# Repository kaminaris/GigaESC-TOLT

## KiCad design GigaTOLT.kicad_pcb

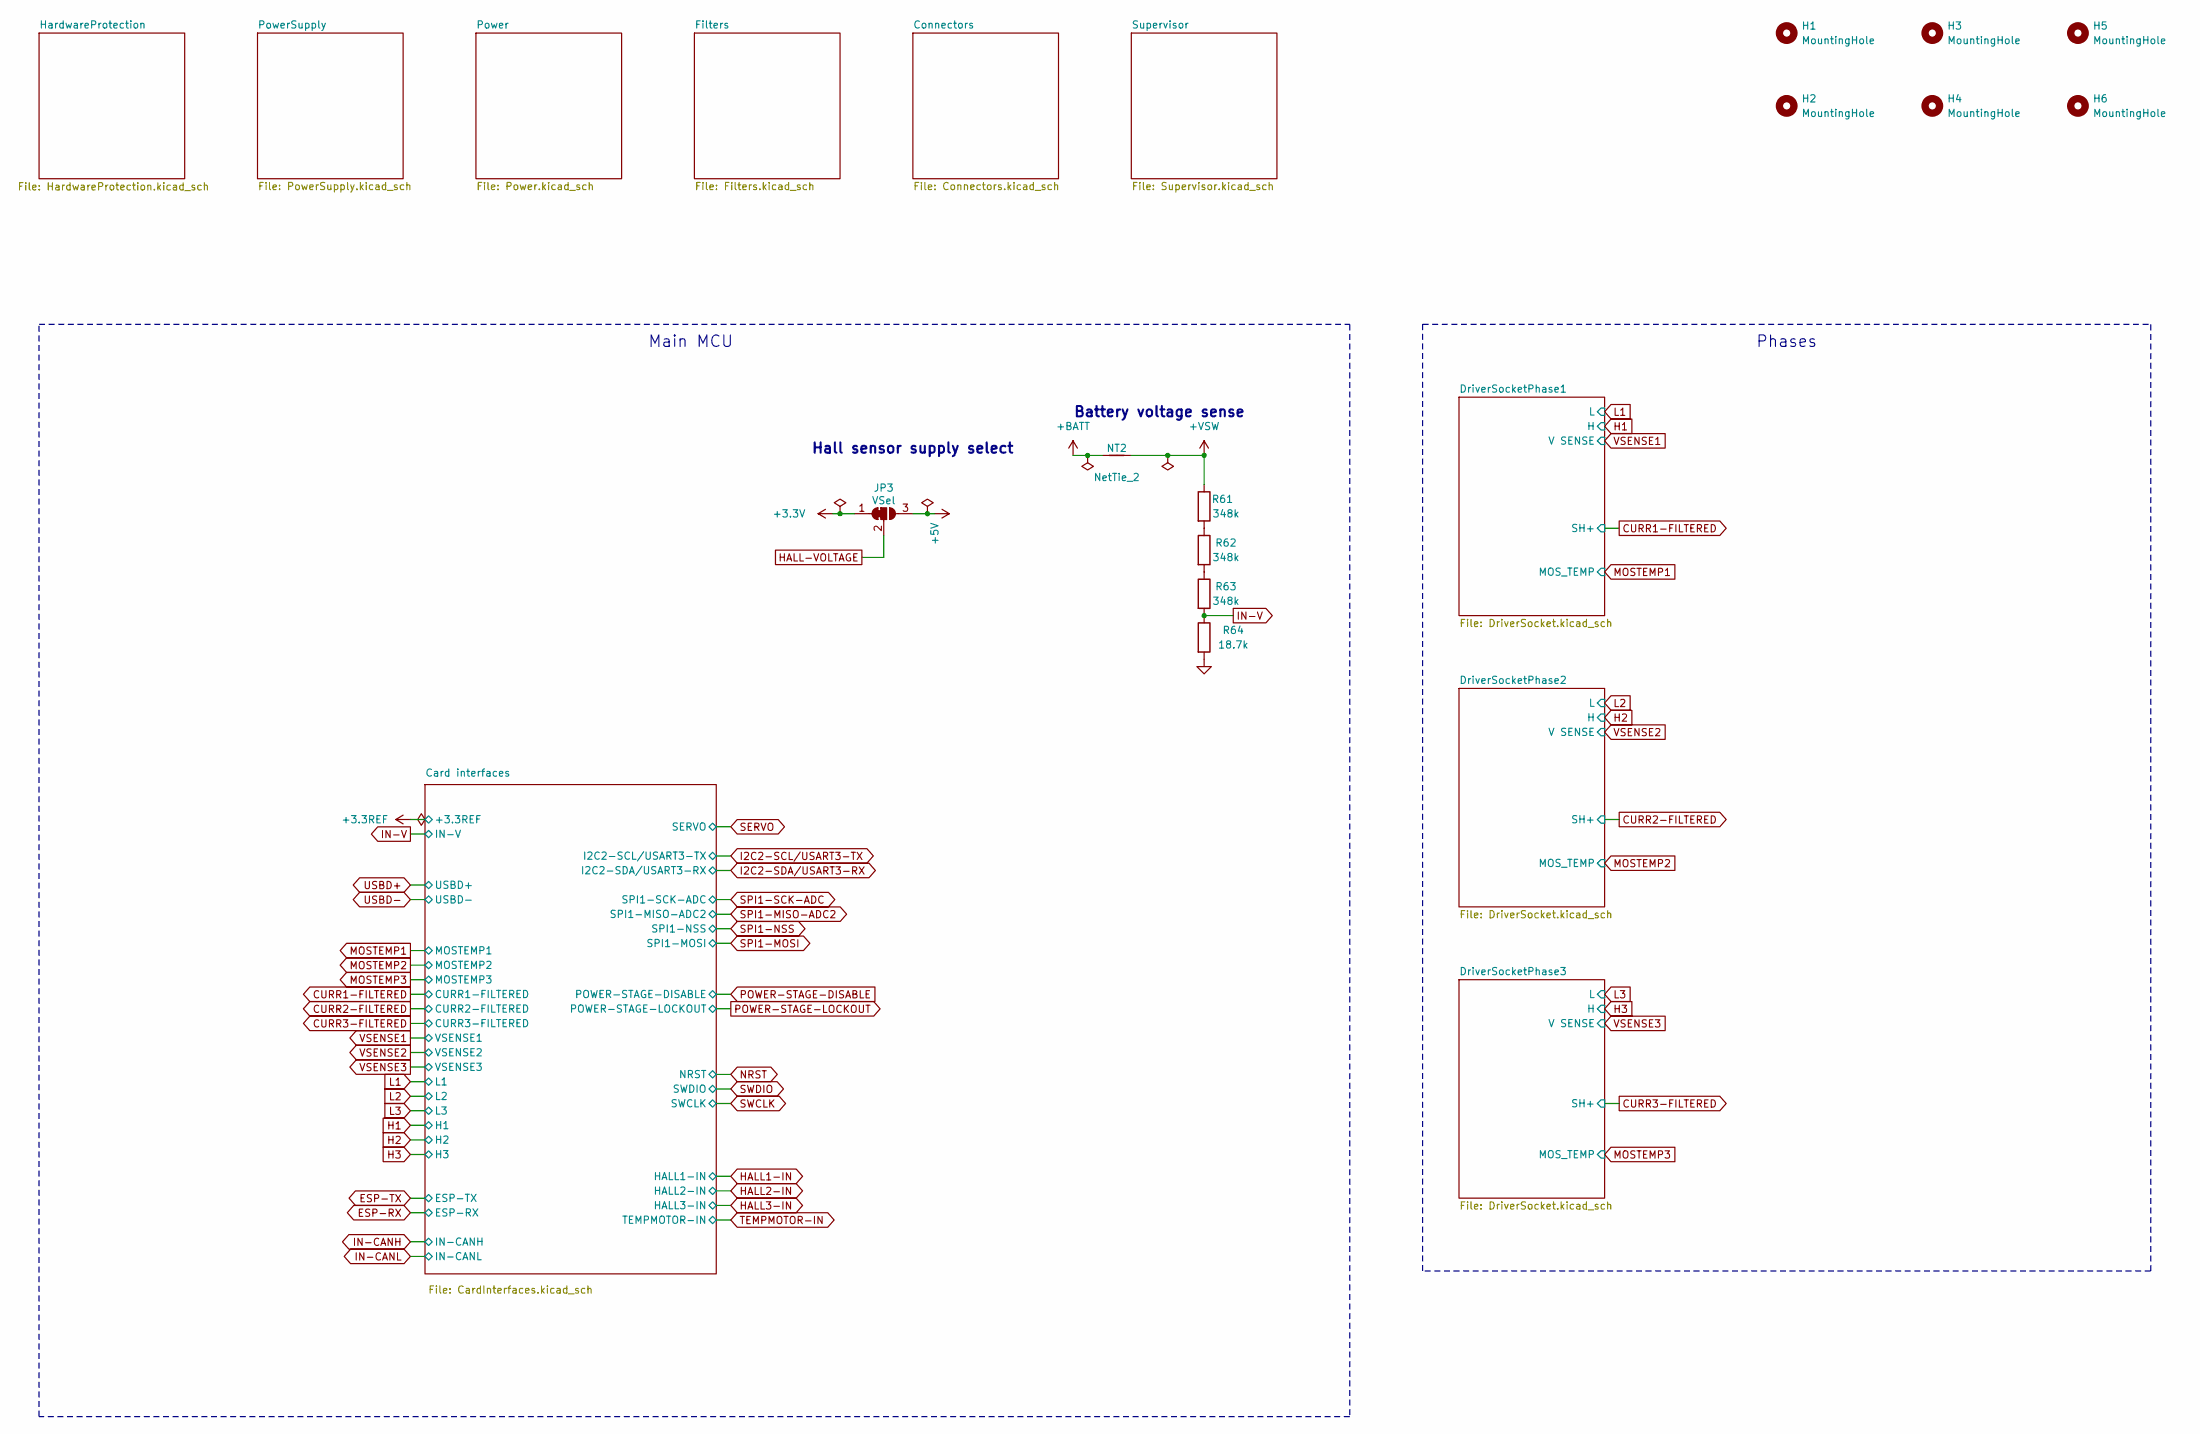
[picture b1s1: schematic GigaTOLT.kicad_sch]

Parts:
H1, H2, H3, H4, H5, H6: MountingHole; CapHead_3.5mm
JP3: VSel; SolderJumper-3-0.5-Small
NT2: NetTie_2; NetTie-2_SMD_Pad0.5mm
R61, R62, R63: 348k; R_0603_1608Metric; MPN C23006
R64: 18.7k; R_0603_1608Metric; MPN C22893

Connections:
+3.3V: JP3.1 (A); also elsewhere on the board
+5V: JP3.3 (B); also elsewhere on the board
+BATT: NT2.1; also elsewhere on the board
+VSW: NT2.2, R61.1; also elsewhere on the board
GND: R64.2; also elsewhere on the board
HALL-VOLTAGE: JP3.2 (C); also elsewhere on the board
IN-V: R63.2, R64.1; also elsewhere on the board
unnamed: R61.2, R62.1
unnamed: R62.2, R63.1

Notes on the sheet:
Main MCU
Battery voltage sense
Phases
Hall sensor supply select

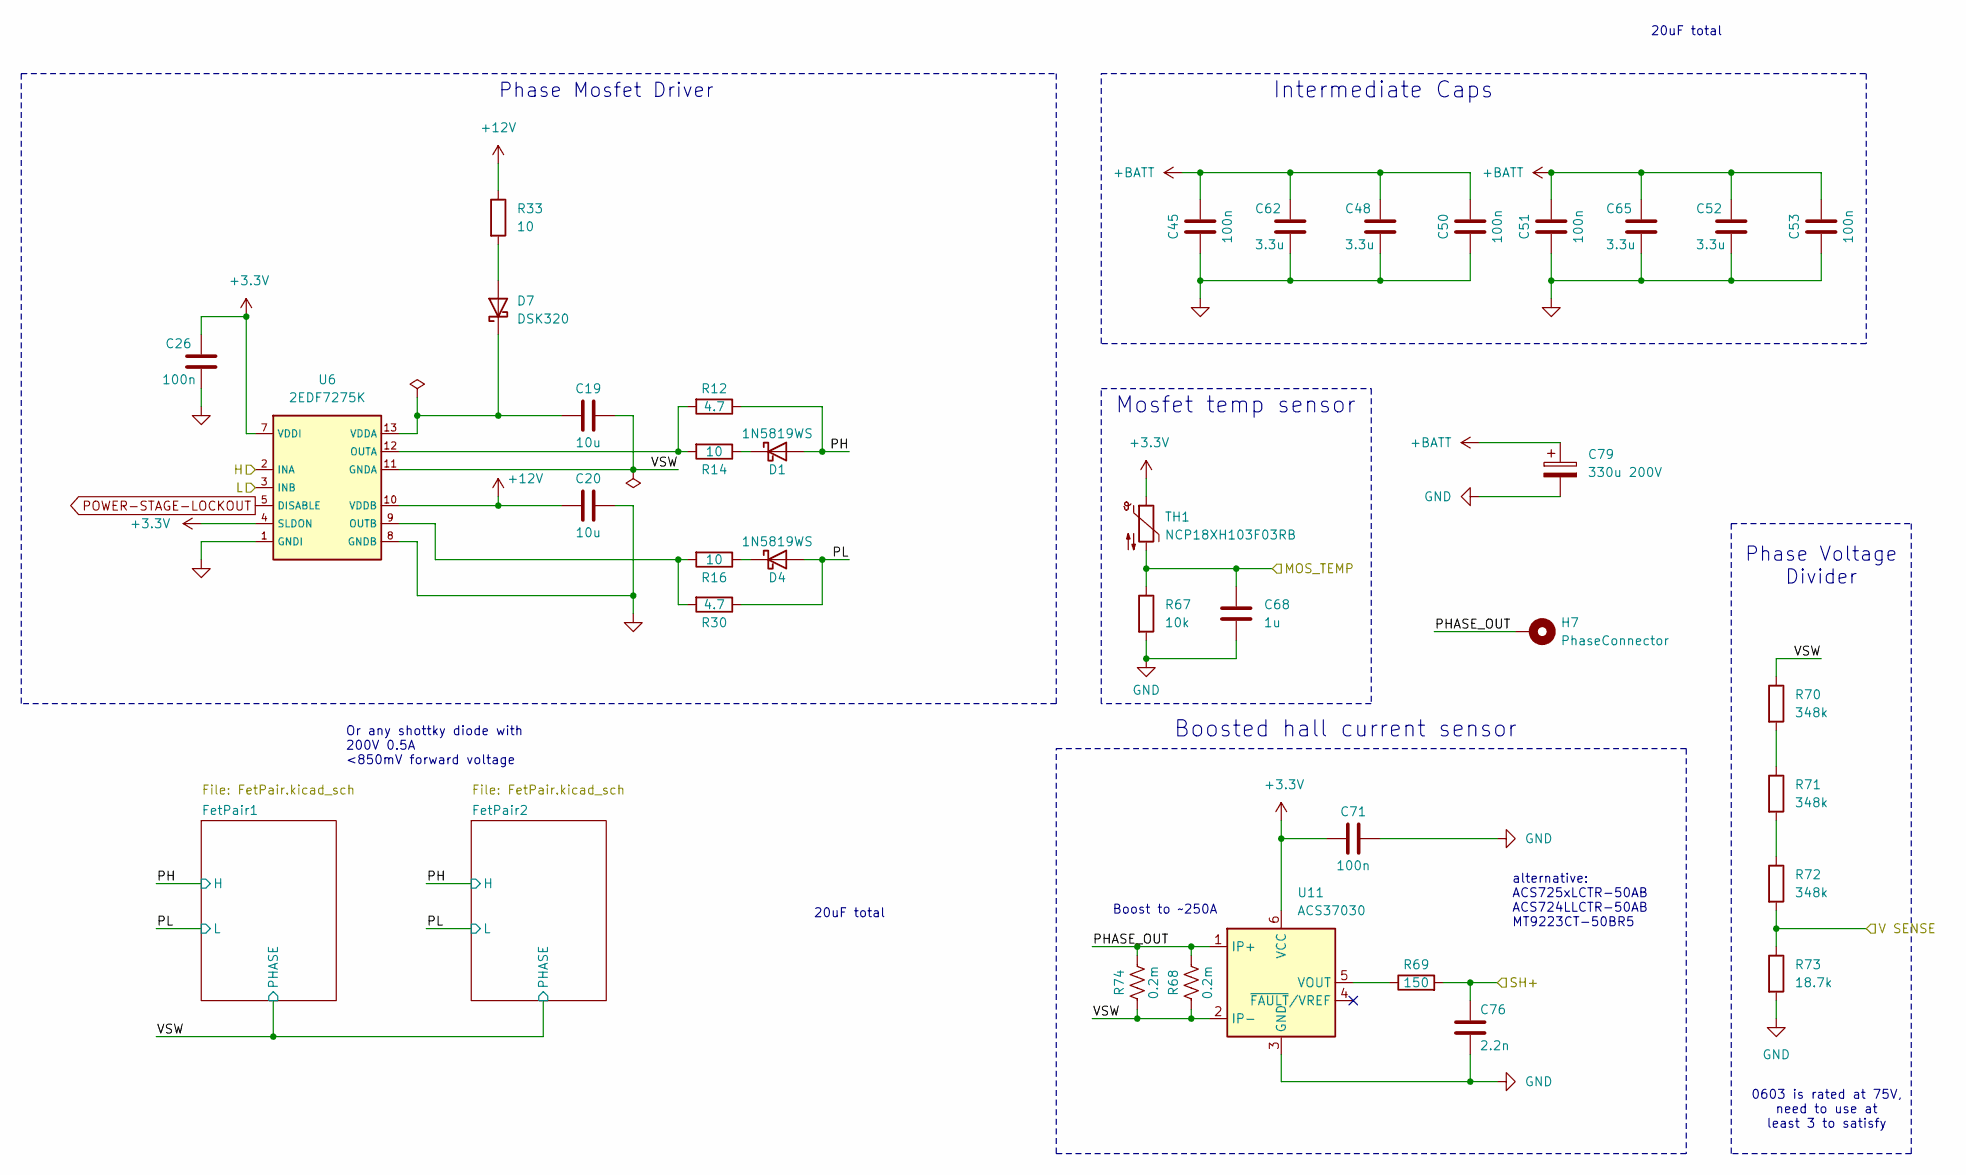
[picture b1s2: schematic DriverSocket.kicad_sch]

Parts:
C19, C20: 10u; C_0805_2012Metric; MPN C1779; Mouser 81-GRM319R61H475KA2D
C26, C71: 100n; C_0603_1608Metric; MPN C14663; Mouser 187-CL21B104KBFNNNE
C45, C50, C51, C53: 100n; C_0805_2012Metric; MPN C784084
C48, C52, C62, C65: 3.3u; C_2220_5750Metric; MPN C22370027; Mouser 81-GRM32EC72A106KE5K
C68: 1u; C_0603_1608Metric; MPN C15849; Mouser 187-CL21B105KPFNNNE
C76: 2.2n; C_0603_1608Metric; MPN C1604
C79: 330u 200V; CapacitorD18x32; MPN C697601; Mouser 661-EKMR201VS222MR50
D1, D4: 1N5819WS; D_SOD-323_HandSoldering; MPN C191023; Mouser 750-SS520B-HF
D7: DSK320; D_SOD-123; MPN C5290222; Mouser 750-SS520B-HF
H7: PhaseConnector; WP-RAFU_7461112
R12, R30: 4.7; R_0603_1608Metric; MPN C22939; Mouser 603-RC0805JR-072R2L
R14, R16, R33: 10; R_0603_1608Metric; MPN C22939; Mouser 603-RC0805JR-072R2L
R67: 10k; R_0603_1608Metric; MPN C25804; Mouser 708-RNCP0805FTD10K0
R68, R74: 0.2m; R_2512_6332Metric; MPN C4944115
R69: 150; R_0603_1608Metric; MPN C22808
R70, R71, R72: 348k; R_0603_1608Metric; MPN C23006; Mouser 603-RC0805FR-07100KL
R73: 18.7k; R_0603_1608Metric; MPN C22893; Mouser 71-CRCW0805-1.8K-E3
TH1: NCP18XH103F03RB; R_0603_1608Metric; MPN C13564; Mouser 81-NCP18XH103F03RB
U6: 2EDF7275K; IC_2EDF7275KXUMA2; MPN C2677063
U11: ACS37030; SOIC-6_3.9x4.9mm_P1.27mm; MPN C22406095

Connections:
+3.3V: C26.2, C71.2, TH1.1, U6.4 (SLDON), U6.7 (VDDI), U11.6 (VCC); also elsewhere on the board
+12V: C20.1, R33.1, U6.10 (VDDB); also elsewhere on the board
+BATT: C45.1, C48.1, C50.1, C51.1, C52.1, C53.1, C62.1, C65.1, C79.1; also elsewhere on the board
/DriverSocketPhase1/PH: D1.2 (A), R12.1; also elsewhere on the board
/DriverSocketPhase1/PHASE_OUT: H7.1 (1_1), R68.2, R74.2, U11.1 (IP+)
/DriverSocketPhase1/PL: D4.2 (A), R30.1; also elsewhere on the board
/DriverSocketPhase1/VSW: C19.2, R68.1, R70.1, R74.1, U6.11 (GNDA), U11.2 (IP-); also elsewhere on the board
CURR1-FILTERED: C76.1, R69.2; also elsewhere on the board
GND: C20.2, C26.1, C45.2, C48.2, C50.2, C51.2, C52.2, C53.2, C62.2, C65.2, C68.2, C71.1, C76.2, C79.2, R67.2, R73.2, U6.1 (GNDI), U6.8 (GNDB), U11.3 (GND); also elsewhere on the board
H1: U6.2 (INA); also elsewhere on the board
L1: U6.3 (INB); also elsewhere on the board
MOSTEMP1: C68.1, R67.1, TH1.2; also elsewhere on the board
unnamed: D1.1 (K), R14.1
unnamed: D4.1 (K), R16.1
unnamed: D7.2 (A), R33.2
unnamed: C19.1, D7.1 (K), U6.13 (VDDA)
unnamed: R70.2, R71.1
unnamed: R71.2, R72.1
unnamed: R12.2, R14.2, U6.12 (OUTA)
unnamed: R16.2, R30.2, U6.9 (OUTB)
unnamed: R69.1, U11.5 (VOUT)
POWER-STAGE-LOCKOUT: U6.5 (DISABLE); also elsewhere on the board
VSENSE1: R72.2, R73.1; also elsewhere on the board

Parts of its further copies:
C21, C22, C24, C25: 10u; C_0805_2012Metric; MPN C1779; Mouser 81-GRM319R61H475KA2D
C28, C29, C101, C131: 100n; C_0603_1608Metric; MPN C14663; Mouser 187-CL21B104KBFNNNE
C46, C47, C54, C56, C58, C59, C60, C69: 100n; C_0805_2012Metric; MPN C784084
C49, C55, C57, C61, C63, C64, C66, C67: 3.3u; C_2220_5750Metric; MPN C22370027; Mouser 81-GRM32EC72A106KE5K
C98, C128: 1u; C_0603_1608Metric; MPN C15849; Mouser 187-CL21B105KPFNNNE
C106, C136: 2.2n; C_0603_1608Metric; MPN C1604
C109, C139: 330u 200V; CapacitorD18x32; MPN C697601; Mouser 661-EKMR201VS222MR50
D2, D3, D5, D6: 1N5819WS; D_SOD-323_HandSoldering; MPN C191023; Mouser 750-SS520B-HF
D8, D9: DSK320; D_SOD-123; MPN C5290222; Mouser 750-SS520B-HF
H8, H9: PhaseConnector; WP-RAFU_7461112
R13, R15, R31, R32: 4.7; R_0603_1608Metric; MPN C22939; Mouser 603-RC0805JR-072R2L
R20, R29, R36, R37, R38, R39: 10; R_0603_1608Metric; MPN C22939; Mouser 603-RC0805JR-072R2L
R75, R76, R81, R98: 0.2m; R_2512_6332Metric; MPN C4944115
R80, R97: 10k; R_0603_1608Metric; MPN C25804; Mouser 708-RNCP0805FTD10K0
R82, R99: 150; R_0603_1608Metric; MPN C22808
R83, R84, R85, R100, R101, R102: 348k; R_0603_1608Metric; MPN C23006; Mouser 603-RC0805FR-07100KL
R86, R103: 18.7k; R_0603_1608Metric; MPN C22893; Mouser 71-CRCW0805-1.8K-E3
TH2, TH3: NCP18XH103F03RB; R_0603_1608Metric; MPN C13564; Mouser 81-NCP18XH103F03RB
U7, U8: 2EDF7275K; IC_2EDF7275KXUMA2; MPN C2677063
U13, U15: ACS37030; SOIC-6_3.9x4.9mm_P1.27mm; MPN C22406095

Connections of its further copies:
+3.3V: C28.2, C29.2, C101.2, C131.2, TH2.1, TH3.1, U7.4 (SLDON), U7.7 (VDDI), U8.4 (SLDON), U8.7 (VDDI), U13.6 (VCC), U15.6 (VCC); also elsewhere on the board
+12V: C22.1, C25.1, R36.1, R37.1, U7.10 (VDDB), U8.10 (VDDB); also elsewhere on the board
+BATT: C46.1, C47.1, C49.1, C54.1, C55.1, C56.1, C57.1, C58.1, C59.1, C60.1, C61.1, C63.1, C64.1, C66.1, C67.1, C69.1, C109.1, C139.1; also elsewhere on the board
/DriverSocketPhase2/PH: D2.2 (A), R13.1; also elsewhere on the board
/DriverSocketPhase2/PHASE_OUT: H8.1 (1_1), R75.2, R81.2, U13.1 (IP+)
/DriverSocketPhase2/PL: D5.2 (A), R31.1; also elsewhere on the board
/DriverSocketPhase2/VSW: C21.2, R75.1, R81.1, R83.1, U7.11 (GNDA), U13.2 (IP-); also elsewhere on the board
/DriverSocketPhase3/PH: D3.2 (A), R15.1; also elsewhere on the board
/DriverSocketPhase3/PHASE_OUT: H9.1 (1_1), R76.2, R98.2, U15.1 (IP+)
/DriverSocketPhase3/PL: D6.2 (A), R32.1; also elsewhere on the board
/DriverSocketPhase3/VSW: C24.2, R76.1, R98.1, R100.1, U8.11 (GNDA), U15.2 (IP-); also elsewhere on the board
CURR2-FILTERED: C106.1, R82.2; also elsewhere on the board
CURR3-FILTERED: C136.1, R99.2; also elsewhere on the board
GND: C22.2, C25.2, C28.1, C29.1, C46.2, C47.2, C49.2, C54.2, C55.2, C56.2, C57.2, C58.2, C59.2, C60.2, C61.2, C63.2, C64.2, C66.2, C67.2, C69.2, C98.2, C101.1, C106.2, C109.2, C128.2, C131.1, C136.2, C139.2, R80.2, R86.2, R97.2, R103.2, U7.1 (GNDI), U7.8 (GNDB), U8.1 (GNDI), U8.8 (GNDB), U13.3 (GND), U15.3 (GND); also elsewhere on the board
H2: U7.2 (INA); also elsewhere on the board
H3: U8.2 (INA); also elsewhere on the board
L2: U7.3 (INB); also elsewhere on the board
L3: U8.3 (INB); also elsewhere on the board
MOSTEMP2: C98.1, R80.1, TH2.2; also elsewhere on the board
MOSTEMP3: C128.1, R97.1, TH3.2; also elsewhere on the board
unnamed: D2.1 (K), R38.1
unnamed: D3.1 (K), R39.1
unnamed: D5.1 (K), R20.1
unnamed: D6.1 (K), R29.1
unnamed: D8.2 (A), R36.2
unnamed: C21.1, D8.1 (K), U7.13 (VDDA)
unnamed: D9.2 (A), R37.2
unnamed: C24.1, D9.1 (K), U8.13 (VDDA)
unnamed: R83.2, R84.1
unnamed: R84.2, R85.1
unnamed: R100.2, R101.1
unnamed: R101.2, R102.1
unnamed: R13.2, R38.2, U7.12 (OUTA)
unnamed: R20.2, R31.2, U7.9 (OUTB)
unnamed: R15.2, R39.2, U8.12 (OUTA)
unnamed: R29.2, R32.2, U8.9 (OUTB)
unnamed: R82.1, U13.5 (VOUT)
unnamed: R99.1, U15.5 (VOUT)
POWER-STAGE-LOCKOUT: U7.5 (DISABLE), U8.5 (DISABLE); also elsewhere on the board
VSENSE2: R85.2, R86.1; also elsewhere on the board
VSENSE3: R102.2, R103.1; also elsewhere on the board

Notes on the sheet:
20uF total
Phase Mosfet Driver
alternative: ACS725xLCTR-50AB ACS724LLCTR-50AB MT9223CT-50BR5
0603 is rated at 75V, need to use at least 3 to satisfy
Boosted hall current sensor
Phase Voltage Divider
Mosfet temp sensor
Boost to ~250A
Or any shottky diode with 200V 0.5A <850mV forward voltage
Intermediate Caps

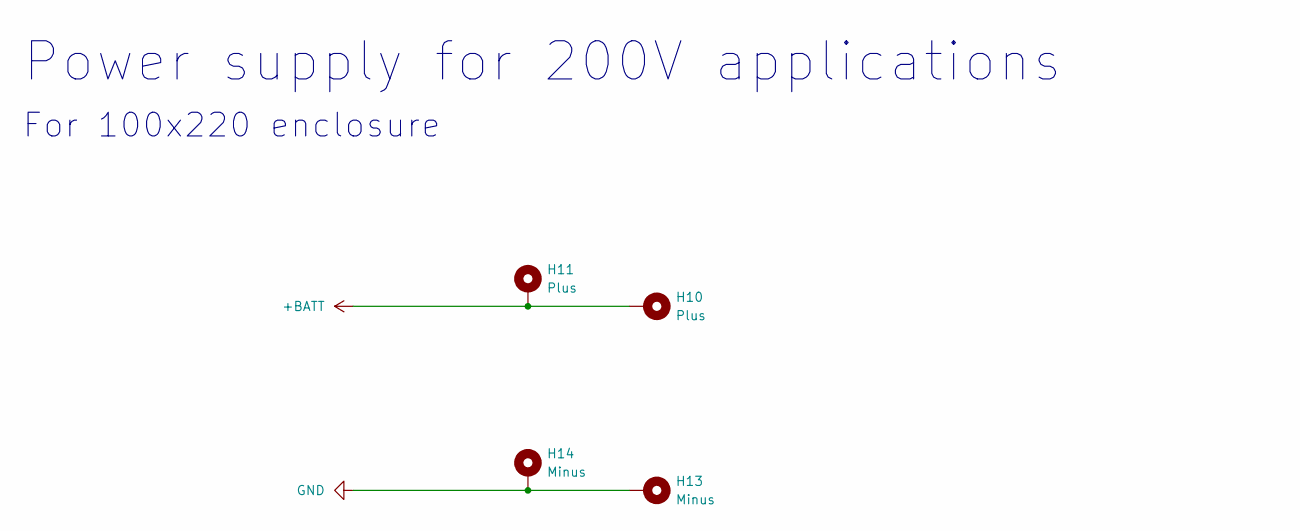
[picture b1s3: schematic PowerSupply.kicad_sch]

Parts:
H10: Plus; WP-RAFU_7461112
H11: Plus; BusBar_5x2mm_L90
H13: Minus; WP-RAFU_7461112
H14: Minus; BusBar_5x2mm_L90

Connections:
+BATT: H10.1 (1_1), H11.1 (1_1); also elsewhere on the board
GND: H13.1 (1_1), H14.1 (1_1); also elsewhere on the board

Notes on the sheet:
Power supply for 200V applications
For 100x220 enclosure

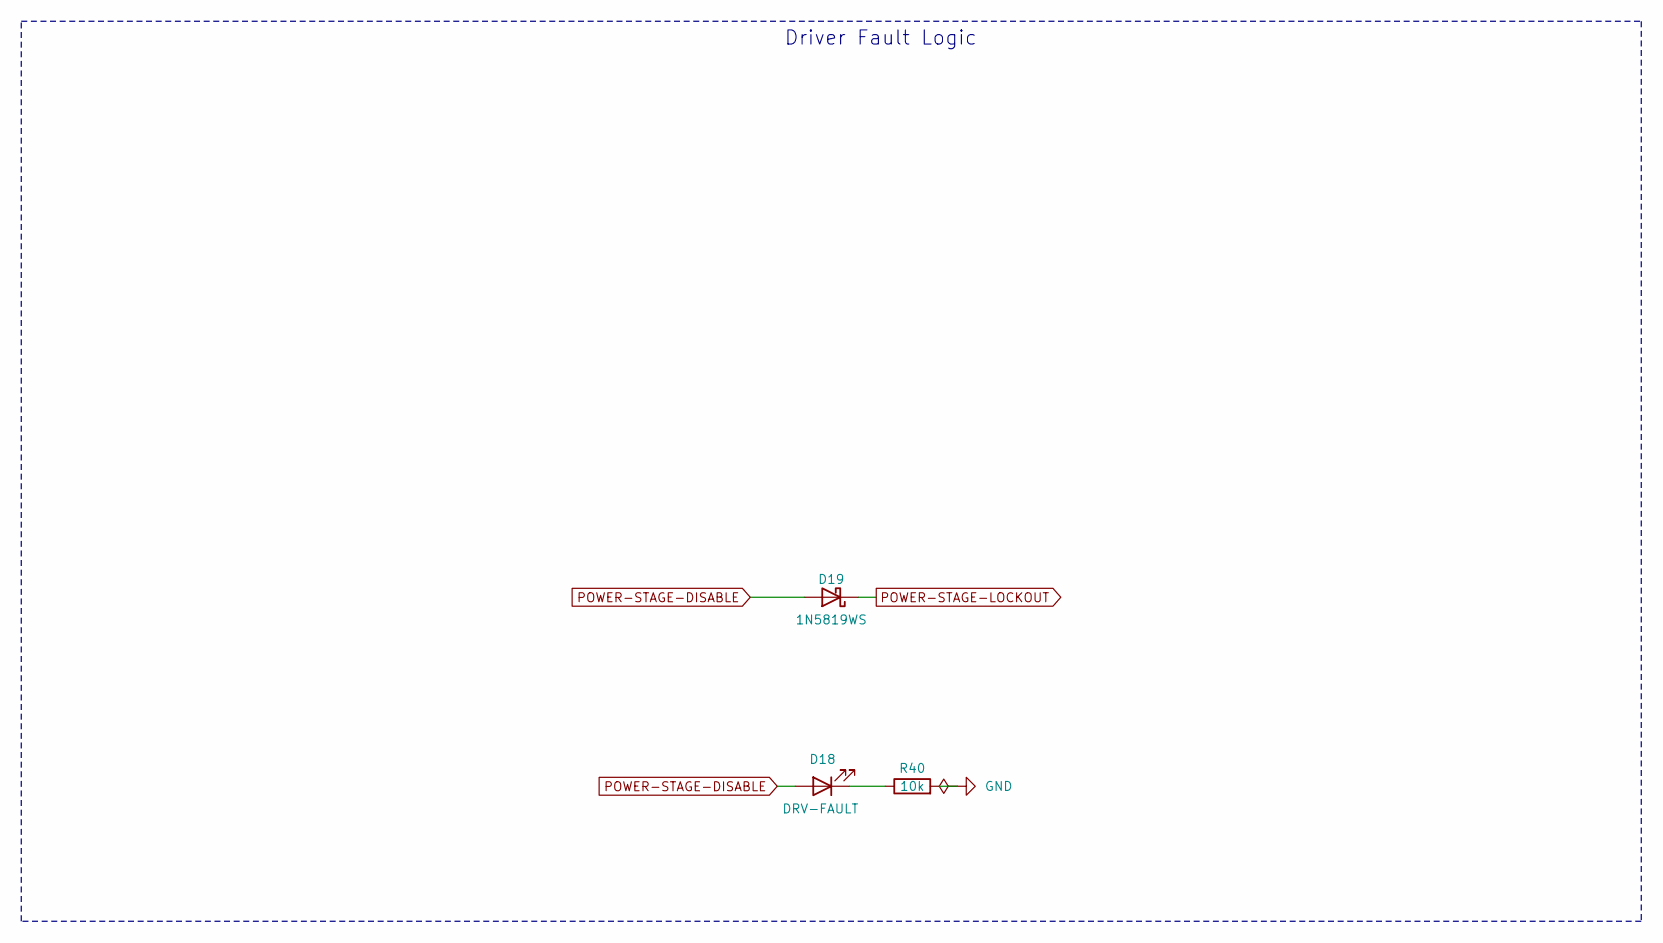
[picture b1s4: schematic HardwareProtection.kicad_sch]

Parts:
D18: DRV-FAULT; LED_0603_1608Metric; MPN C2286
D19: 1N5819WS; D_SOD-323_HandSoldering; MPN C191023
R40: 10k; R_0603_1608Metric; MPN C25804

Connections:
GND: R40.2; also elsewhere on the board
unnamed: D18.1 (K), R40.1
POWER-STAGE-DISABLE: D18.2 (A), D19.2 (A); also elsewhere on the board
POWER-STAGE-LOCKOUT: D19.1 (K); also elsewhere on the board

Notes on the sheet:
Driver Fault Logic

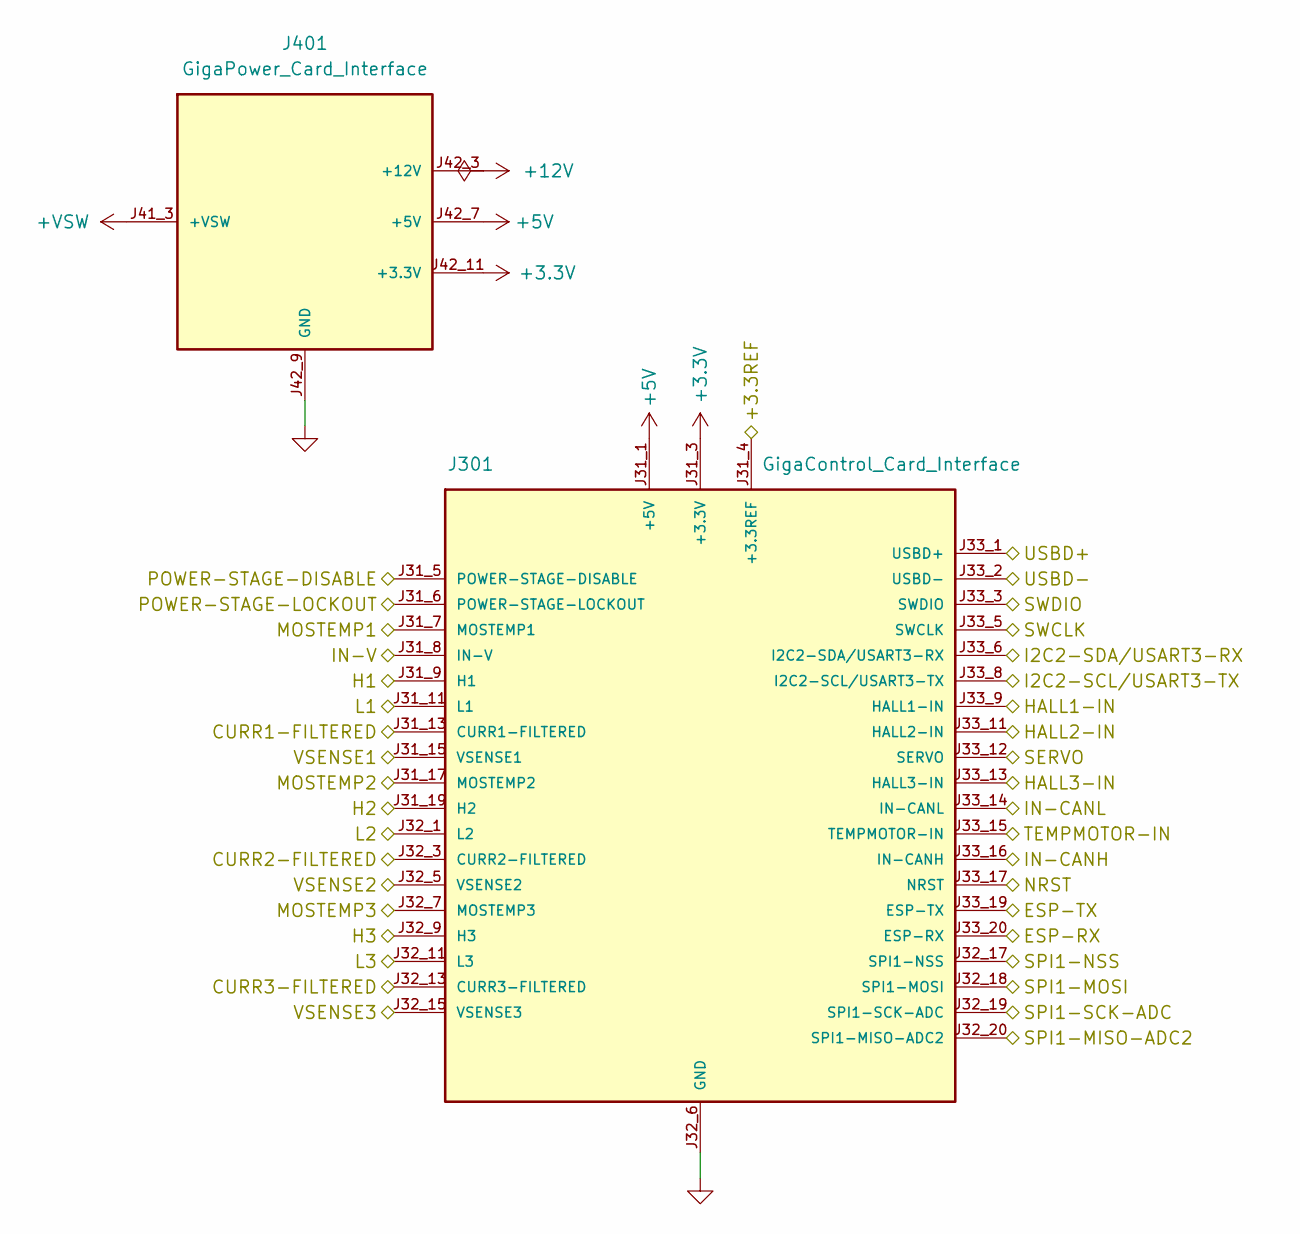
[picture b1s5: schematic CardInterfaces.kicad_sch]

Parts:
J301: GigaControl_Card_Interface
J401: GigaPower_Card_Interface

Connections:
+3.3REF: J301.J31_4 (+3.3REF)
+3.3V: J301.J31_3 (+3.3V), J401.J42_11 (+3.3V), J401.J42_12 (+3.3V); also elsewhere on the board
+5V: J301.J31_1 (+5V), J401.J42_7 (+5V), J401.J42_8 (+5V); also elsewhere on the board
+12V: J401.J42_3 (+12V), J401.J42_4 (+12V); also elsewhere on the board
+VSW: J401.J41_3 (+VSW), J401.J41_5 (+VSW); also elsewhere on the board
CURR1-FILTERED: J301.J31_13 (CURR1-FILTERED); also elsewhere on the board
CURR2-FILTERED: J301.J32_3 (CURR2-FILTERED); also elsewhere on the board
CURR3-FILTERED: J301.J32_13 (CURR3-FILTERED); also elsewhere on the board
ESP-RX: J301.J33_20 (ESP-RX); also elsewhere on the board
ESP-TX: J301.J33_19 (ESP-TX); also elsewhere on the board
GND: J301.J31_2 (GND), J301.J31_10 (GND), J301.J31_12 (GND), J301.J31_14 (GND), J301.J31_16 (GND), J301.J31_18 (GND), J301.J31_20 (GND), J301.J32_2 (GND), J301.J32_4 (GND), J301.J32_6 (GND), J301.J32_8 (GND), J301.J32_10 (GND), J301.J32_12 (GND), J301.J32_14 (GND), J301.J32_16 (GND), J301.J33_4 (GND), J301.J33_7 (GND), J301.J33_10 (GND), J301.J33_18 (GND), J401.J41_17 (GND), J401.J41_18 (GND), J401.J41_19 (GND), J401.J41_20 (GND), J401.J42_1 (GND), J401.J42_2 (GND), J401.J42_5 (GND), J401.J42_6 (GND), J401.J42_9 (GND), J401.J42_10 (GND), J401.J42_13 (GND), J401.J42_14 (GND), J401.J42_15 (GND), J401.J42_16 (GND), J401.J42_19 (GND), J401.J42_20 (GND); also elsewhere on the board
H1: J301.J31_9 (H1); also elsewhere on the board
H2: J301.J31_19 (H2); also elsewhere on the board
H3: J301.J32_9 (H3); also elsewhere on the board
HALL1-IN: J301.J33_9 (HALL1-IN); also elsewhere on the board
HALL2-IN: J301.J33_11 (HALL2-IN); also elsewhere on the board
HALL3-IN: J301.J33_13 (HALL3-IN); also elsewhere on the board
I2C2-SCL/USART3-TX: J301.J33_8 (I2C2-SCL/USART3-TX); also elsewhere on the board
I2C2-SDA/USART3-RX: J301.J33_6 (I2C2-SDA/USART3-RX); also elsewhere on the board
IN-CANH: J301.J33_16 (IN-CANH); also elsewhere on the board
IN-CANL: J301.J33_14 (IN-CANL); also elsewhere on the board
IN-V: J301.J31_8 (IN-V); also elsewhere on the board
L1: J301.J31_11 (L1); also elsewhere on the board
L2: J301.J32_1 (L2); also elsewhere on the board
L3: J301.J32_11 (L3); also elsewhere on the board
MOSTEMP1: J301.J31_7 (MOSTEMP1); also elsewhere on the board
MOSTEMP2: J301.J31_17 (MOSTEMP2); also elsewhere on the board
MOSTEMP3: J301.J32_7 (MOSTEMP3); also elsewhere on the board
NRST: J301.J33_17 (NRST); also elsewhere on the board
POWER-STAGE-DISABLE: J301.J31_5 (POWER-STAGE-DISABLE); also elsewhere on the board
POWER-STAGE-LOCKOUT: J301.J31_6 (POWER-STAGE-LOCKOUT); also elsewhere on the board
SERVO: J301.J33_12 (SERVO); also elsewhere on the board
SPI1-MISO-ADC2: J301.J32_20 (SPI1-MISO-ADC2); also elsewhere on the board
SPI1-MOSI: J301.J32_18 (SPI1-MOSI); also elsewhere on the board
SPI1-NSS: J301.J32_17 (SPI1-NSS); also elsewhere on the board
SPI1-SCK-ADC: J301.J32_19 (SPI1-SCK-ADC); also elsewhere on the board
SWCLK: J301.J33_5 (SWCLK); also elsewhere on the board
SWDIO: J301.J33_3 (SWDIO); also elsewhere on the board
TEMPMOTOR-IN: J301.J33_15 (TEMPMOTOR-IN); also elsewhere on the board
USBD+: J301.J33_1 (USBD+); also elsewhere on the board
USBD-: J301.J33_2 (USBD-); also elsewhere on the board
VSENSE1: J301.J31_15 (VSENSE1); also elsewhere on the board
VSENSE2: J301.J32_5 (VSENSE2); also elsewhere on the board
VSENSE3: J301.J32_15 (VSENSE3); also elsewhere on the board

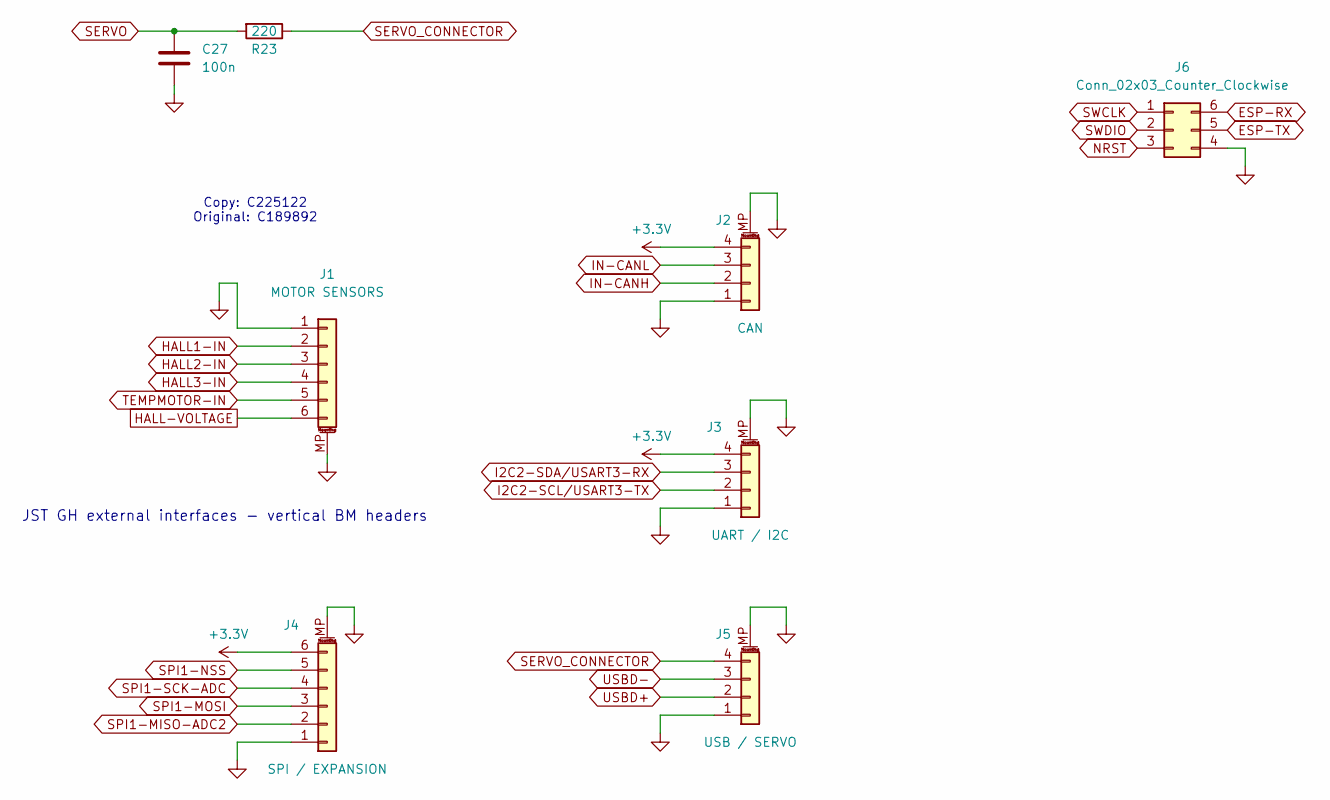
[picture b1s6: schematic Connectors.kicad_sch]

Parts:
C27: 100n; C_0402_1005Metric; MPN C1525
J1: MOTOR SENSORS; JST_GH_BM06B-GHS-TBT_1x06-1MP_P1.25mm_Vertical; MPN C225122
J2: CAN; JST_GH_BM04B-GHS-TBT_1x04-1MP_P1.25mm_Vertical; MPN C161692
J3: UART / I2C; JST_GH_BM04B-GHS-TBT_1x04-1MP_P1.25mm_Vertical; MPN C161692
J4: SPI / EXPANSION; JST_GH_BM06B-GHS-TBT_1x06-1MP_P1.25mm_Vertical; MPN C225122
J5: USB / SERVO; JST_GH_BM04B-GHS-TBT_1x04-1MP_P1.25mm_Vertical; MPN C161692
J6: Conn_02x03_Counter_Clockwise; PinHeader_2x03_P1.00mm_Vertical; MPN C22438180
R23: 220; R_0603_1608Metric; MPN C22962

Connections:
+3.3V: J2.4, J3.4, J4.6; also elsewhere on the board
ESP-RX: J6.6; also elsewhere on the board
ESP-TX: J6.5; also elsewhere on the board
GND: C27.2, J1.1, J1.MP (MountPin), J2.1, J2.MP (MountPin), J3.1, J3.MP (MountPin), J4.1, J4.MP (MountPin), J5.1, J5.MP (MountPin), J6.4; also elsewhere on the board
HALL1-IN: J1.2; also elsewhere on the board
HALL2-IN: J1.3; also elsewhere on the board
HALL3-IN: J1.4; also elsewhere on the board
HALL-VOLTAGE: J1.6; also elsewhere on the board
I2C2-SCL/USART3-TX: J3.2; also elsewhere on the board
I2C2-SDA/USART3-RX: J3.3; also elsewhere on the board
IN-CANH: J2.2; also elsewhere on the board
IN-CANL: J2.3; also elsewhere on the board
NRST: J6.3; also elsewhere on the board
SERVO: C27.1, R23.2; also elsewhere on the board
SERVO_CONNECTOR: J5.4, R23.1
SPI1-MISO-ADC2: J4.2; also elsewhere on the board
SPI1-MOSI: J4.3; also elsewhere on the board
SPI1-NSS: J4.5; also elsewhere on the board
SPI1-SCK-ADC: J4.4; also elsewhere on the board
SWCLK: J6.1; also elsewhere on the board
SWDIO: J6.2; also elsewhere on the board
TEMPMOTOR-IN: J1.5; also elsewhere on the board
USBD+: J5.2; also elsewhere on the board
USBD-: J5.3; also elsewhere on the board

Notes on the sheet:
Copy: C225122 Original: C189892
JST GH external interfaces - vertical BM headers

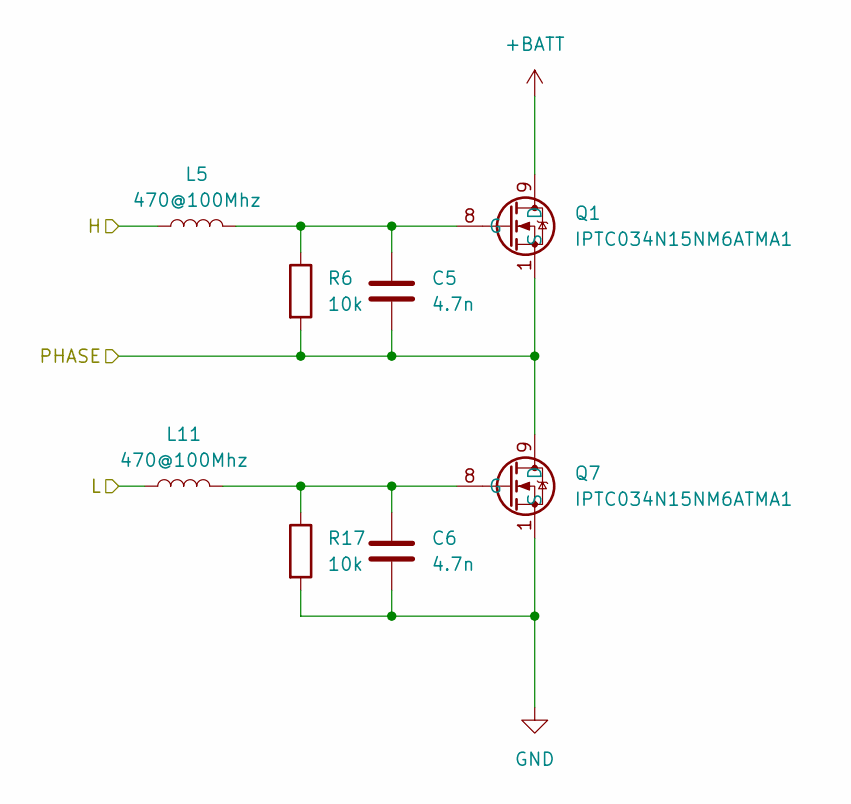
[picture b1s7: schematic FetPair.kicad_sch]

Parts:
C5, C6: 4.7n; C_0603_1608Metric; MPN C53987
L5, L11: 470@100Mhz; L_0603_1608Metric; MPN C113019
Q1, Q7: IPTC034N15NM6ATMA1; TOLT; MPN C3280341
R6, R17: 10k; R_0603_1608Metric; MPN C25804; Mouser 708-RNCP0805FTD10K0

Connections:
+BATT: Q1.9 (D), Q1.10 (D_2), Q1.11 (D_3), Q1.12 (D_4), Q1.13 (D_5), Q1.14 (D_6), Q1.15 (D_7), Q1.16 (D_8); also elsewhere on the board
/DriverSocketPhase1/PH: L5.1; also elsewhere on the board
/DriverSocketPhase1/PL: L11.1; also elsewhere on the board
/DriverSocketPhase1/VSW: C5.2, Q1.1 (S), Q1.2 (S_2), Q1.3 (S_3), Q1.4 (S_4), Q1.5 (S_5), Q1.6 (S_6), Q1.7 (S_7), Q7.9 (D), Q7.10 (D_2), Q7.11 (D_3), Q7.12 (D_4), Q7.13 (D_5), Q7.14 (D_6), Q7.15 (D_7), Q7.16 (D_8), R6.2; also elsewhere on the board
GND: C6.2, Q7.1 (S), Q7.2 (S_2), Q7.3 (S_3), Q7.4 (S_4), Q7.5 (S_5), Q7.6 (S_6), Q7.7 (S_7), R17.2; also elsewhere on the board
unnamed: C5.1, L5.2, Q1.8 (G), R6.1
unnamed: C6.1, L11.2, Q7.8 (G), R17.1

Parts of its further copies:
C10, C11, C12, C13, C14, C15, C16, C17, C18, C23: 4.7n; C_0603_1608Metric; MPN C53987
L9, L10, L12, L13, L14, L15, L16, L17, L18, L19: 470@100Mhz; L_0603_1608Metric; MPN C113019
Q2, Q3, Q5, Q6, Q8, Q9, Q10, Q23, Q24, Q25: IPTC034N15NM6ATMA1; TOLT; MPN C3280341
R7, R8, R18, R19, R24, R25, R26, R27, R28, R35: 10k; R_0603_1608Metric; MPN C25804; Mouser 708-RNCP0805FTD10K0

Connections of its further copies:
+BATT: Q2.9 (D), Q2.10 (D_2), Q2.11 (D_3), Q2.12 (D_4), Q2.13 (D_5), Q2.14 (D_6), Q2.15 (D_7), Q2.16 (D_8), Q3.9 (D), Q3.10 (D_2), Q3.11 (D_3), Q3.12 (D_4), Q3.13 (D_5), Q3.14 (D_6), Q3.15 (D_7), Q3.16 (D_8), Q5.9 (D), Q5.10 (D_2), Q5.11 (D_3), Q5.12 (D_4), Q5.13 (D_5), Q5.14 (D_6), Q5.15 (D_7), Q5.16 (D_8), Q6.9 (D), Q6.10 (D_2), Q6.11 (D_3), Q6.12 (D_4), Q6.13 (D_5), Q6.14 (D_6), Q6.15 (D_7), Q6.16 (D_8), Q10.9 (D), Q10.10 (D_2), Q10.11 (D_3), Q10.12 (D_4), Q10.13 (D_5), Q10.14 (D_6), Q10.15 (D_7), Q10.16 (D_8); also elsewhere on the board
/DriverSocketPhase1/PH: L14.1; also elsewhere on the board
/DriverSocketPhase1/PL: L15.1; also elsewhere on the board
/DriverSocketPhase1/VSW: C15.2, Q5.1 (S), Q5.2 (S_2), Q5.3 (S_3), Q5.4 (S_4), Q5.5 (S_5), Q5.6 (S_6), Q5.7 (S_7), Q23.9 (D), Q23.10 (D_2), Q23.11 (D_3), Q23.12 (D_4), Q23.13 (D_5), Q23.14 (D_6), Q23.15 (D_7), Q23.16 (D_8), R26.2; also elsewhere on the board
/DriverSocketPhase2/PH: L9.1, L18.1; also elsewhere on the board
/DriverSocketPhase2/PL: L12.1, L16.1; also elsewhere on the board
/DriverSocketPhase2/VSW: C10.2, C17.2, Q2.1 (S), Q2.2 (S_2), Q2.3 (S_3), Q2.4 (S_4), Q2.5 (S_5), Q2.6 (S_6), Q2.7 (S_7), Q6.1 (S), Q6.2 (S_2), Q6.3 (S_3), Q6.4 (S_4), Q6.5 (S_5), Q6.6 (S_6), Q6.7 (S_7), Q8.9 (D), Q8.10 (D_2), Q8.11 (D_3), Q8.12 (D_4), Q8.13 (D_5), Q8.14 (D_6), Q8.15 (D_7), Q8.16 (D_8), Q24.9 (D), Q24.10 (D_2), Q24.11 (D_3), Q24.12 (D_4), Q24.13 (D_5), Q24.14 (D_6), Q24.15 (D_7), Q24.16 (D_8), R7.2, R27.2; also elsewhere on the board
/DriverSocketPhase3/PH: L10.1, L19.1; also elsewhere on the board
/DriverSocketPhase3/PL: L13.1, L17.1; also elsewhere on the board
/DriverSocketPhase3/VSW: C12.2, C23.2, Q3.1 (S), Q3.2 (S_2), Q3.3 (S_3), Q3.4 (S_4), Q3.5 (S_5), Q3.6 (S_6), Q3.7 (S_7), Q9.9 (D), Q9.10 (D_2), Q9.11 (D_3), Q9.12 (D_4), Q9.13 (D_5), Q9.14 (D_6), Q9.15 (D_7), Q9.16 (D_8), Q10.1 (S), Q10.2 (S_2), Q10.3 (S_3), Q10.4 (S_4), Q10.5 (S_5), Q10.6 (S_6), Q10.7 (S_7), Q25.9 (D), Q25.10 (D_2), Q25.11 (D_3), Q25.12 (D_4), Q25.13 (D_5), Q25.14 (D_6), Q25.15 (D_7), Q25.16 (D_8), R8.2, R28.2; also elsewhere on the board
GND: C11.2, C13.2, C14.2, C16.2, C18.2, Q8.1 (S), Q8.2 (S_2), Q8.3 (S_3), Q8.4 (S_4), Q8.5 (S_5), Q8.6 (S_6), Q8.7 (S_7), Q9.1 (S), Q9.2 (S_2), Q9.3 (S_3), Q9.4 (S_4), Q9.5 (S_5), Q9.6 (S_6), Q9.7 (S_7), Q23.1 (S), Q23.2 (S_2), Q23.3 (S_3), Q23.4 (S_4), Q23.5 (S_5), Q23.6 (S_6), Q23.7 (S_7), Q24.1 (S), Q24.2 (S_2), Q24.3 (S_3), Q24.4 (S_4), Q24.5 (S_5), Q24.6 (S_6), Q24.7 (S_7), Q25.1 (S), Q25.2 (S_2), Q25.3 (S_3), Q25.4 (S_4), Q25.5 (S_5), Q25.6 (S_6), Q25.7 (S_7), R18.2, R19.2, R24.2, R25.2, R35.2; also elsewhere on the board
unnamed: C10.1, L9.2, Q2.8 (G), R7.1
unnamed: C12.1, L10.2, Q3.8 (G), R8.1
unnamed: C15.1, L14.2, Q5.8 (G), R26.1
unnamed: C17.1, L18.2, Q6.8 (G), R27.1
unnamed: C11.1, L12.2, Q8.8 (G), R18.1
unnamed: C13.1, L13.2, Q9.8 (G), R19.1
unnamed: C23.1, L19.2, Q10.8 (G), R28.1
unnamed: C16.1, L15.2, Q23.8 (G), R24.1
unnamed: C18.1, L16.2, Q24.8 (G), R25.1
unnamed: C14.1, L17.2, Q25.8 (G), R35.1
